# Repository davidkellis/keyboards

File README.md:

# TKL keyboard designs

Low-profile tenkeyless keyboard designs, from the original KiCad project to
later nRF52840 boards, case designs, and switch-plate lighting experiments.
The repository contains PCB and schematic sources, mechanical models,
manufacturing exports, firmware configuration notes, and interactive 3D viewers.

*V12 assembly visualization. Fit, lighting, and alternate switch-family support
still require physical prototype testing.*

## Start here

The latest revision is **[TKL v12](tkl/tkl12/README.md)**: an 86-key PCB with
soldered mounting patterns for Kailh Choc V1, Kailh Choc V2, and selected Gateron
Low Profile 3.0 switches. Its case and plate requirements depend on the chosen
switch family; see the [compatibility notes](tkl/tkl12/SWITCHES.md).

- **Explore the design:** clone or download the repository, then open
  `tkl/tkl12/render-switches/index.html` locally in Chrome or Brave. The
  [switch and keycap studio](tkl/tkl12/render-switches/README.md) works offline.
- **Open the CAD:** use [keyboard.kicad_pro](tkl/tkl12/kicad/keyboard.kicad_pro)
  in KiCad 10 to inspect the latest PCB and schematic.
- **Review fit models:** start with the
  [PCB models and switch-fit coupon](tkl/tkl12/case/README.md).
- **Review fabrication outputs:** read the
  [ordering notes](tkl/tkl12/manufacturing/ORDERING.md) and
  [fabrication instructions](tkl/tkl12/manufacturing/FABRICATION.md).
- **Check or regenerate exports:** follow the
  [revision's source and checking instructions](tkl/tkl12/scripts/README.md).

Recent revisions are prototypes with software validation records. Hardware
bring-up, switch and stabilizer travel, battery integration, and optical
performance still need physical testing. Read the chosen revision's notes and
[bring-up procedure](tkl/tkl12/BRINGUP.md) before ordering or assembling a board.

## Design revisions

Each major version has one commit. The original project is preserved as v0;
decimal variants stay with their major version. Earlier designs remain in
their own directories so their sources and design choices can be compared.

| Version | Design |
| --- | --- |
| [v0](tkl/tkl0/README.md) | Original KiCad project |
| [v1](tkl/tkl1/README.md) | Initial keyboard layout and KiCad design |
| [v2](tkl/tkl2/) | Early PCB and schematic revision |
| [v3](tkl/tkl3/) | Early PCB and schematic revision |
| [v4](tkl/tkl4/) | PCB and case design |
| [v5](tkl/tkl5/) | PCB and case refinement |
| [v6](tkl/tkl6/) | Controller-module board and case |
| [v7](tkl/tkl7/README.md) | Integrated nRF52840 design and v7.x alternatives |
| [v8](tkl/tkl8/README.md) | Top-mounted LED design |
| [v9](tkl/tkl9/README.md) | Direct rear USB module and v9.x case revisions |
| [v10](tkl/tkl10/README.md) | Esc/F1 controller position, case variants, and lighting studies |
| [v11](tkl/tkl11/README.md) | Reverse LEDs and acrylic switch plate |
| [v12](tkl/tkl12/README.md) | Multiple soldered low-profile switch families |

v7 alternatives: [v7.3](tkl/tkl7.3/README.md), [v7.4](tkl/tkl7.4/README.md),
and [v7.5](tkl/tkl7.5/README.md).

v9 case revisions: [v9.1](tkl/tkl9.1/README.md), [v9.2](tkl/tkl9.2/README.md),
and [v9.3](tkl/tkl9.3/README.md).

Shared [mechanical tools](tkl/mechanical/README.md), [research](tkl/research/),
and [handoff packaging](tkl/package_handoff.py) support the later designs.

## Finding the files

Recent revision directories use the following structure:

| Path | Contents |
| --- | --- |
| `kicad/` | PCB, schematic, project settings, and local component libraries |
| `case/` | Mechanical models, print-fit gauges, and fit documentation |
| `manufacturing/` | Gerbers and drills, BOM and placement files, assembly drawings, and ordering notes |
| `firmware/` | Controller, matrix, and lighting configuration references |
| `scripts/` | Design generation, export, and validation tools |
| `validation/` | Saved electrical, mechanical, and export check results |
| `reference/` | Manufacturer drawings, design studies, and preserved source records |
| `render-*/` | Browser viewers, assembly previews, and rendering sources |

The original v0 and v1 KiCad projects retain their `tkl.kicad_pro` filenames
directly inside `tkl/tkl0/` and `tkl/tkl1/`.

Use the PCB, manufacturing files, and mechanical parts from the same revision
unless its documentation explicitly identifies a compatible earlier part.
Print-fit gauges intentionally enlarge some holes; use the Gerber and drill
exports for PCB fabrication.

## Working with the sources

Recent electrical designs use KiCad 10. Python generators may need KiCad's
`pcbnew` module and additional geometry packages; mechanical tools use CadQuery,
and viewer generators have their own Python or Node dependencies. Follow the
instructions and dependency files beside the tool you want to run.

The final routed PCB is the source for normal checks and manufacturing exports.
Some revision-building scripts reset from an earlier baseline or change routing;
read their instructions before running them.

## Third-party credits

Rendering studies include third-party software and meshes. See the
[v12 viewer attributions](tkl/tkl12/render-switches/ATTRIBUTIONS.md) and the
attribution and license files included with each rendering study.

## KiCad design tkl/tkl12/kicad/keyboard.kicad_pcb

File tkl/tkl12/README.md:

# TKL V12 — three soldered low-profile switch families

V12 is a separate revision derived from the final routed V11 board. **V11 and
earlier revisions are preserved.** Open [the KiCad project](kicad/keyboard.kicad_pro)
or [the PCB](kicad/keyboard.kicad_pcb).

Explore the assembled keyboard in the new [V12 switch and keycap studio](render-switches/index.html):
switch families, matching keycap styles, both case editions, free 360° viewing,
exploded layers and lighting previews. Appearance and alternate-family mechanical
fit assumptions are explained in the [viewer notes](render-switches/README.md).

The board retains every original Kailh Choc V2 drill, copper land and switch
position. Each of the 86 keys gains two shared nonplated locating slots and two
Gateron electrical contacts. Choose one switch family for the build:

| Family | PCB mounting | Other parts needed |
| --- | --- | --- |
| Kailh Choc V2, including our Deep Sea Mini Whale | Original holes and contacts, unchanged | Existing Kailh plate height and MX-stem keycaps |
| Kailh Choc V1 | Original electrical contacts plus shared side slots | Choc two-slot keycaps; verify stabilizers and cap/case travel |
| Selected Gateron Low Profile 3.0 | Alternate contacts plus shared side slots | Plate top 2.5 mm above PCB instead of Kailh's 2.2 mm; verify keycap skirts, travel and optics |

These are **soldered footprints**, without hot-swap sockets. The exact Gateron
references and mounting drawing are in [SWITCHES.md](SWITCHES.md). This does not
claim compatibility with older Gateron generations, Cherry Low Profile or every
retail switch sold under a similar name.

The three-family pattern uses the same LED-facing direction. The earlier
feasibility study mixed top and bottom drawing views for Gateron; V12 corrects
that chirality and checks it against the official PCB drawing and KiCad's
standard MX footprint. One output capacitor, **C2**, moves from (117.8, 31) to
(124, 34.5) mm to clear the added contacts. All other component positions,
the boost switching loop, LED positions, matrix, controller pinout, board outline
and twelve M2 mounting holes remain unchanged.

## Assembly and cost

The target stays **two layers, 1.6 mm FR-4, lead-free HASL and lead-free Economic
bottom-side assembly**. The factory BOM is unchanged: ten purchasing groups and
106 placements, all on the bottom. Switches and the controller clone are fitted
by the user. The new holes do not add SMT placements or feeder types; extra
drilling/routing can still affect the fabrication quote. The current live quote is linked below; it retains the previous $29.05 fabrication price for five.

The ten reverse LEDs, TPS61169 driver, ZMK PWM interface and optional four-LED
wire bypass retain V11's circuit. See [bring-up instructions](BRINGUP.md).
Changing switch family does not require a different electrical matrix or pinmap.

## Files and checks

- [Front copper preview](front.svg) and [back copper preview](back.svg).
- [Switch mounting diagram](reference/switch-pattern.svg).
- [Manufacturing package](manufacturing/tkl-v12-prototype-handoff.zip), including
  Gerbers/drills, schematic PDF, assembly drawings, BOM and CPL.
- [Ordering settings](manufacturing/ORDERING.md) and [fabrication notes](manufacturing/FABRICATION.md).
- [Exact PCB STL](case/pcb-bare.stl) and [enlarged-hole print gauge](case/pcb-fit-check.stl).
- [Small three-position print-fit coupon](case/switch-fit-coupon.stl).
- [Electrical checks](validation/summary.json), [preservation and pattern audit](validation/revision-audit.json)
  and [export checks](validation/handoff-check.json).
- [Repeatable checking/export commands](scripts/README.md).

The existing V11/V10 case and plate remain the reference for our Kailh build;
V12 does not silently change their switch seating height. There is no completed
Gateron-height case/plate in this PCB revision. The print coupon checks pin and
peg alignment, not metal PCB tolerances, switch clip retention or optical performance.
Test real switches, plate, stabilizers and keycap travel before buying a complete
alternate-family build. Hardware, charging, RF and lighting still need prototype
bench tests; software checks do not establish physical performance.

Final software checks (KiCad 10, 2026-10-16): **0 ERC errors/warnings,
0 DRC errors/warnings, 0 unrouted connections and 0 schematic parity issues**.
All 86 keys and all 344 new holes are checked. The original V11's 470 saved
files are unchanged. Exported drill coordinates, archive hashes and 106 bottom
placements also pass; all three STL models are watertight.

The [live JLCPCB quote saved on 2026-10-16](manufacturing/quote-v12-2026-10-16/README.md)
is **$180.26 delivered for five assembled boards** using lead-free HASL,
lead-free Economic bottom-side assembly and UPS DDP, before any unpriced
reverse-LED handling/fixture charge after review. Nothing has been ordered or
paid. The displayed PCB fabrication price remains $29.05 for five.

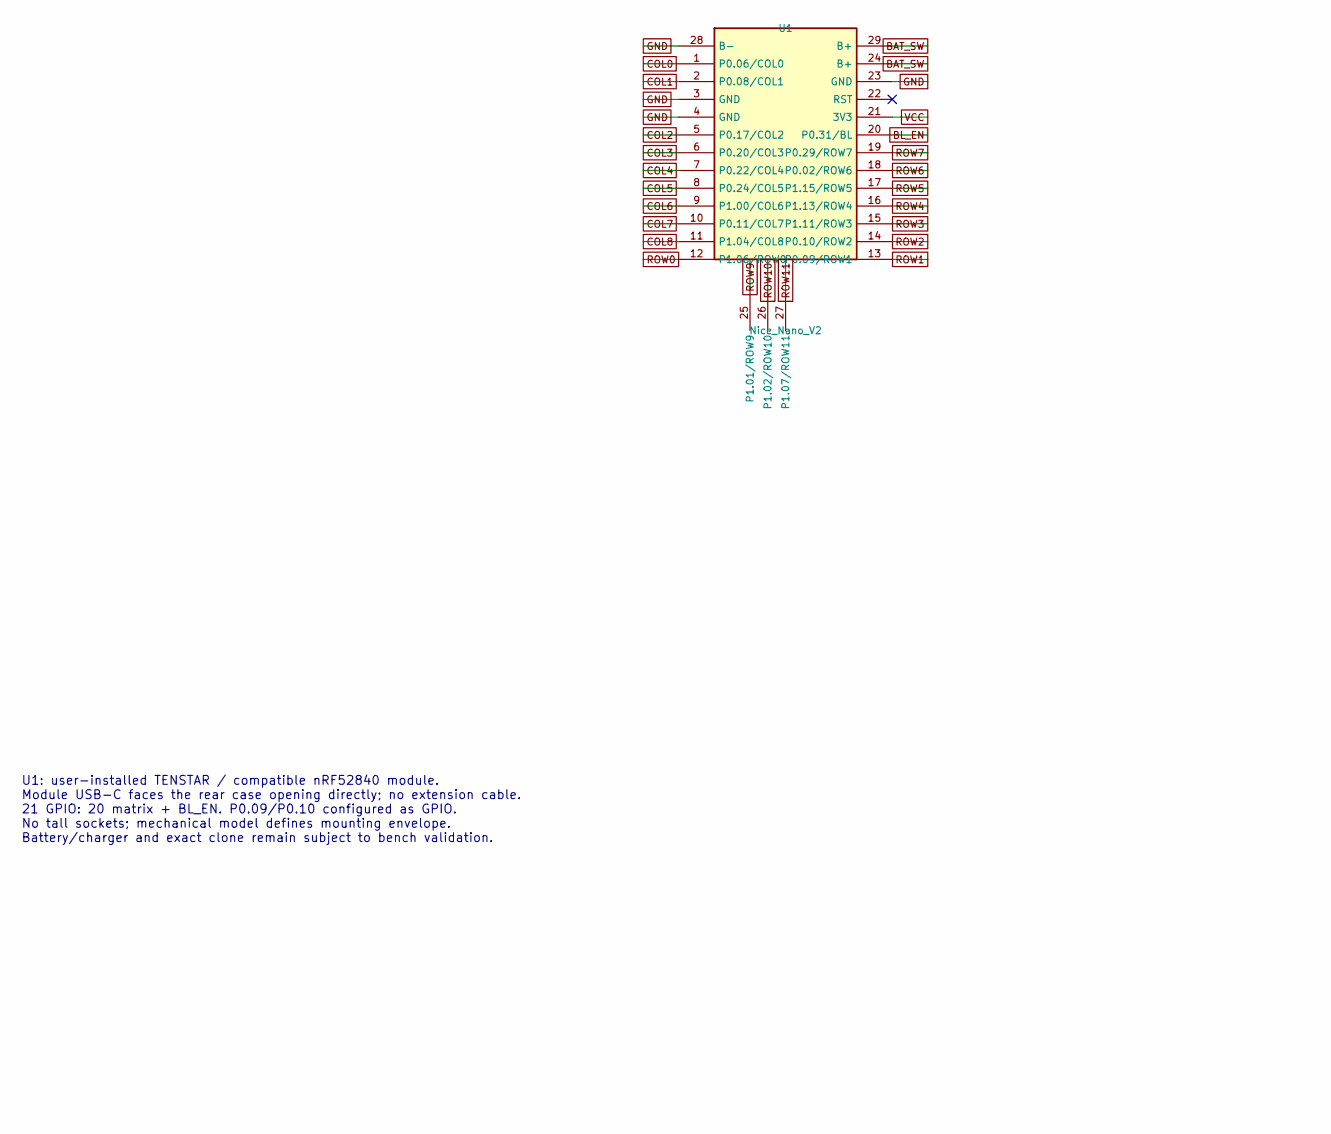
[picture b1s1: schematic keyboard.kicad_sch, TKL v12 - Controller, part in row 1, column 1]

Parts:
U1: Nice_Nano_V2; U1_Nice_Nano_V2

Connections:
BAT_SW: U1.24 (B+), U1.29 (B+); also elsewhere on the board
BL_EN: U1.20 (21); also elsewhere on the board
COL0: U1.1; also elsewhere on the board
COL1: U1.2 (0); also elsewhere on the board
COL2: U1.5 (2); also elsewhere on the board
COL3: U1.6 (3); also elsewhere on the board
COL4: U1.7 (4); also elsewhere on the board
COL5: U1.8 (5); also elsewhere on the board
COL6: U1.9 (6); also elsewhere on the board
COL7: U1.10 (7); also elsewhere on the board
COL8: U1.11 (8); also elsewhere on the board
GND: U1.3 (GND), U1.4 (GND), U1.23 (GND), U1.28 (B-); also elsewhere on the board
ROW0: U1.12 (9); also elsewhere on the board
ROW1: U1.13 (10); also elsewhere on the board
ROW2: U1.14 (16); also elsewhere on the board
ROW3: U1.15 (14); also elsewhere on the board
ROW4: U1.16 (15); also elsewhere on the board
ROW5: U1.17 (18); also elsewhere on the board
ROW6: U1.18 (19); also elsewhere on the board
ROW7: U1.19 (20); also elsewhere on the board
ROW9: U1.25 (1); also elsewhere on the board
ROW10: U1.26 (2); also elsewhere on the board
ROW11: U1.27 (7); also elsewhere on the board
VCC: U1.21 (3.3v)

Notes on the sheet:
U1: user-installed TENSTAR / compatible nRF52840 module. Module USB-C faces the rear case opening directly; no extension cable. 21 GPIO: 20 matrix + BL_EN. P0.09/P0.10 configured as GPIO. No tall sockets; mechanical model defines mounting envelope. Battery/charger and exact clone remain subject to 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

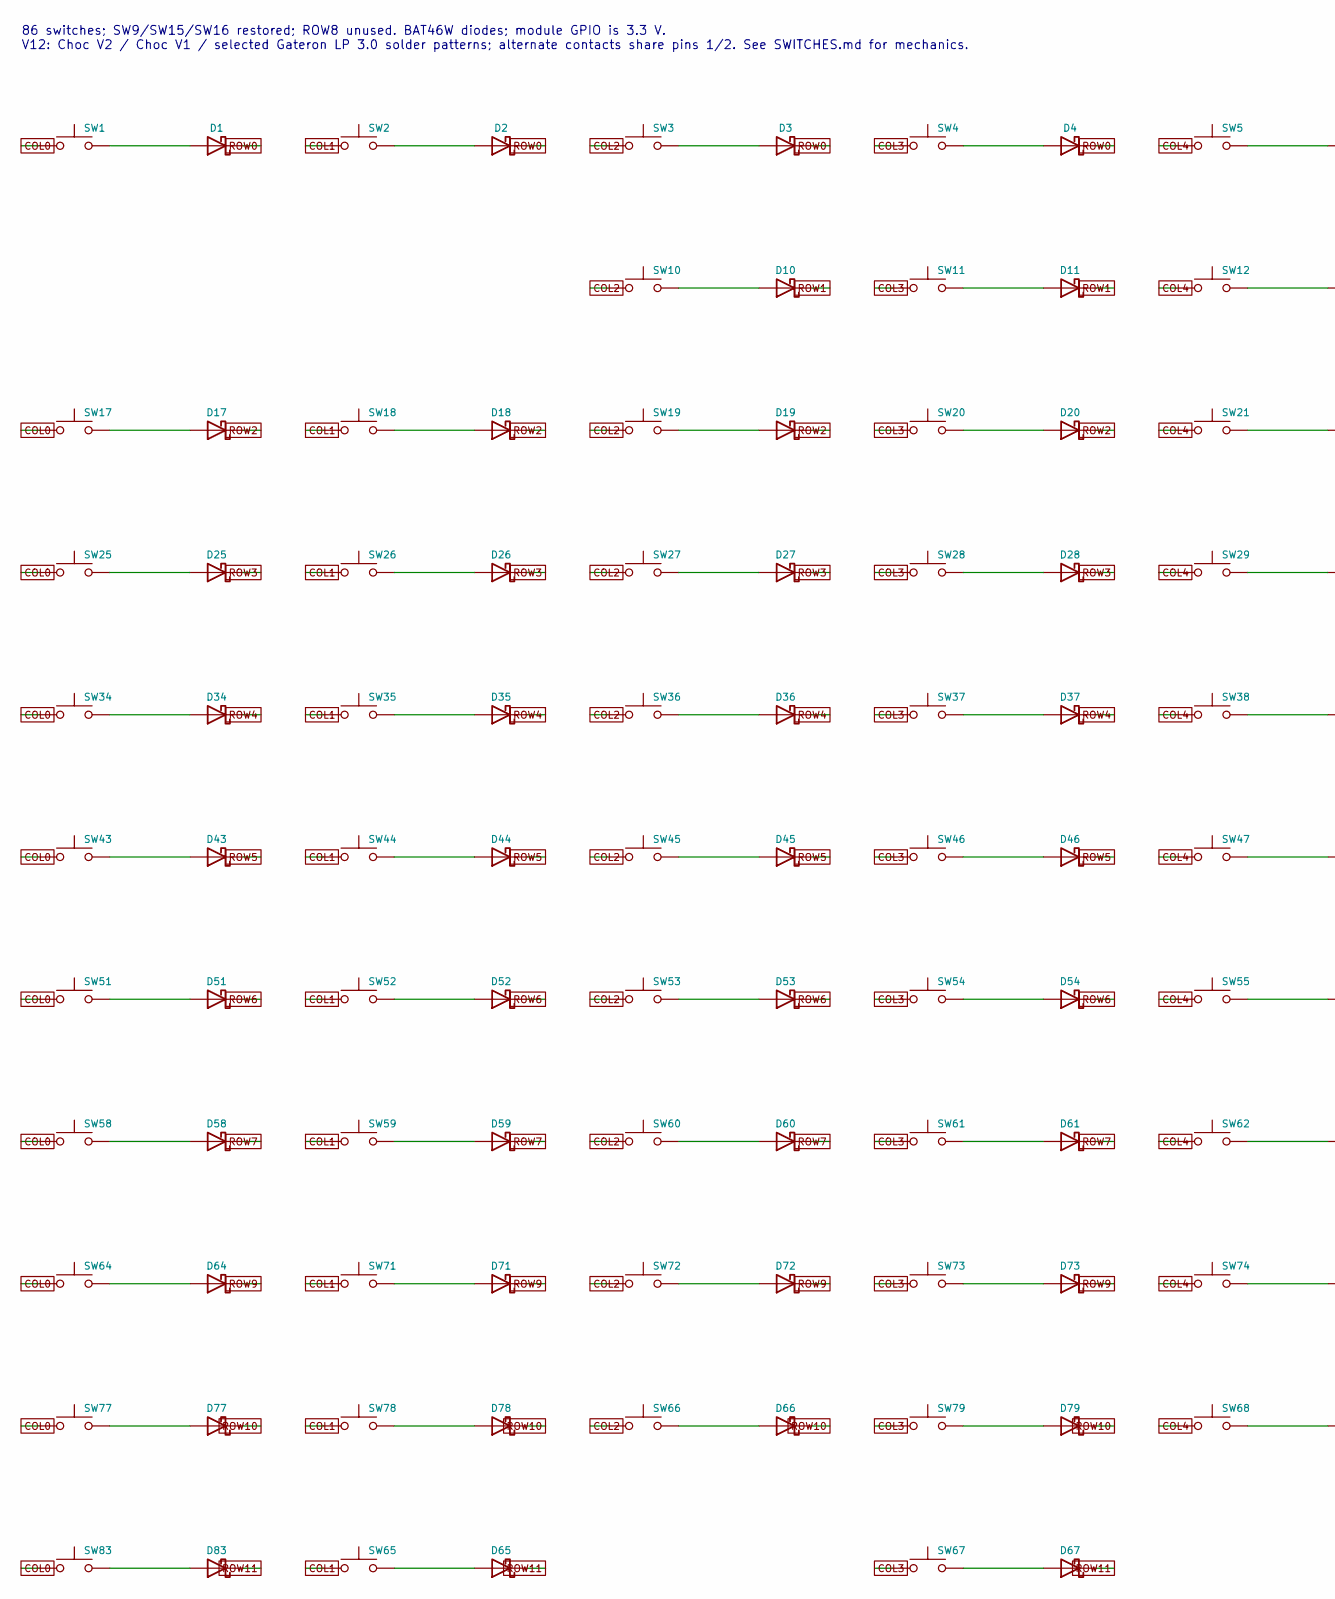
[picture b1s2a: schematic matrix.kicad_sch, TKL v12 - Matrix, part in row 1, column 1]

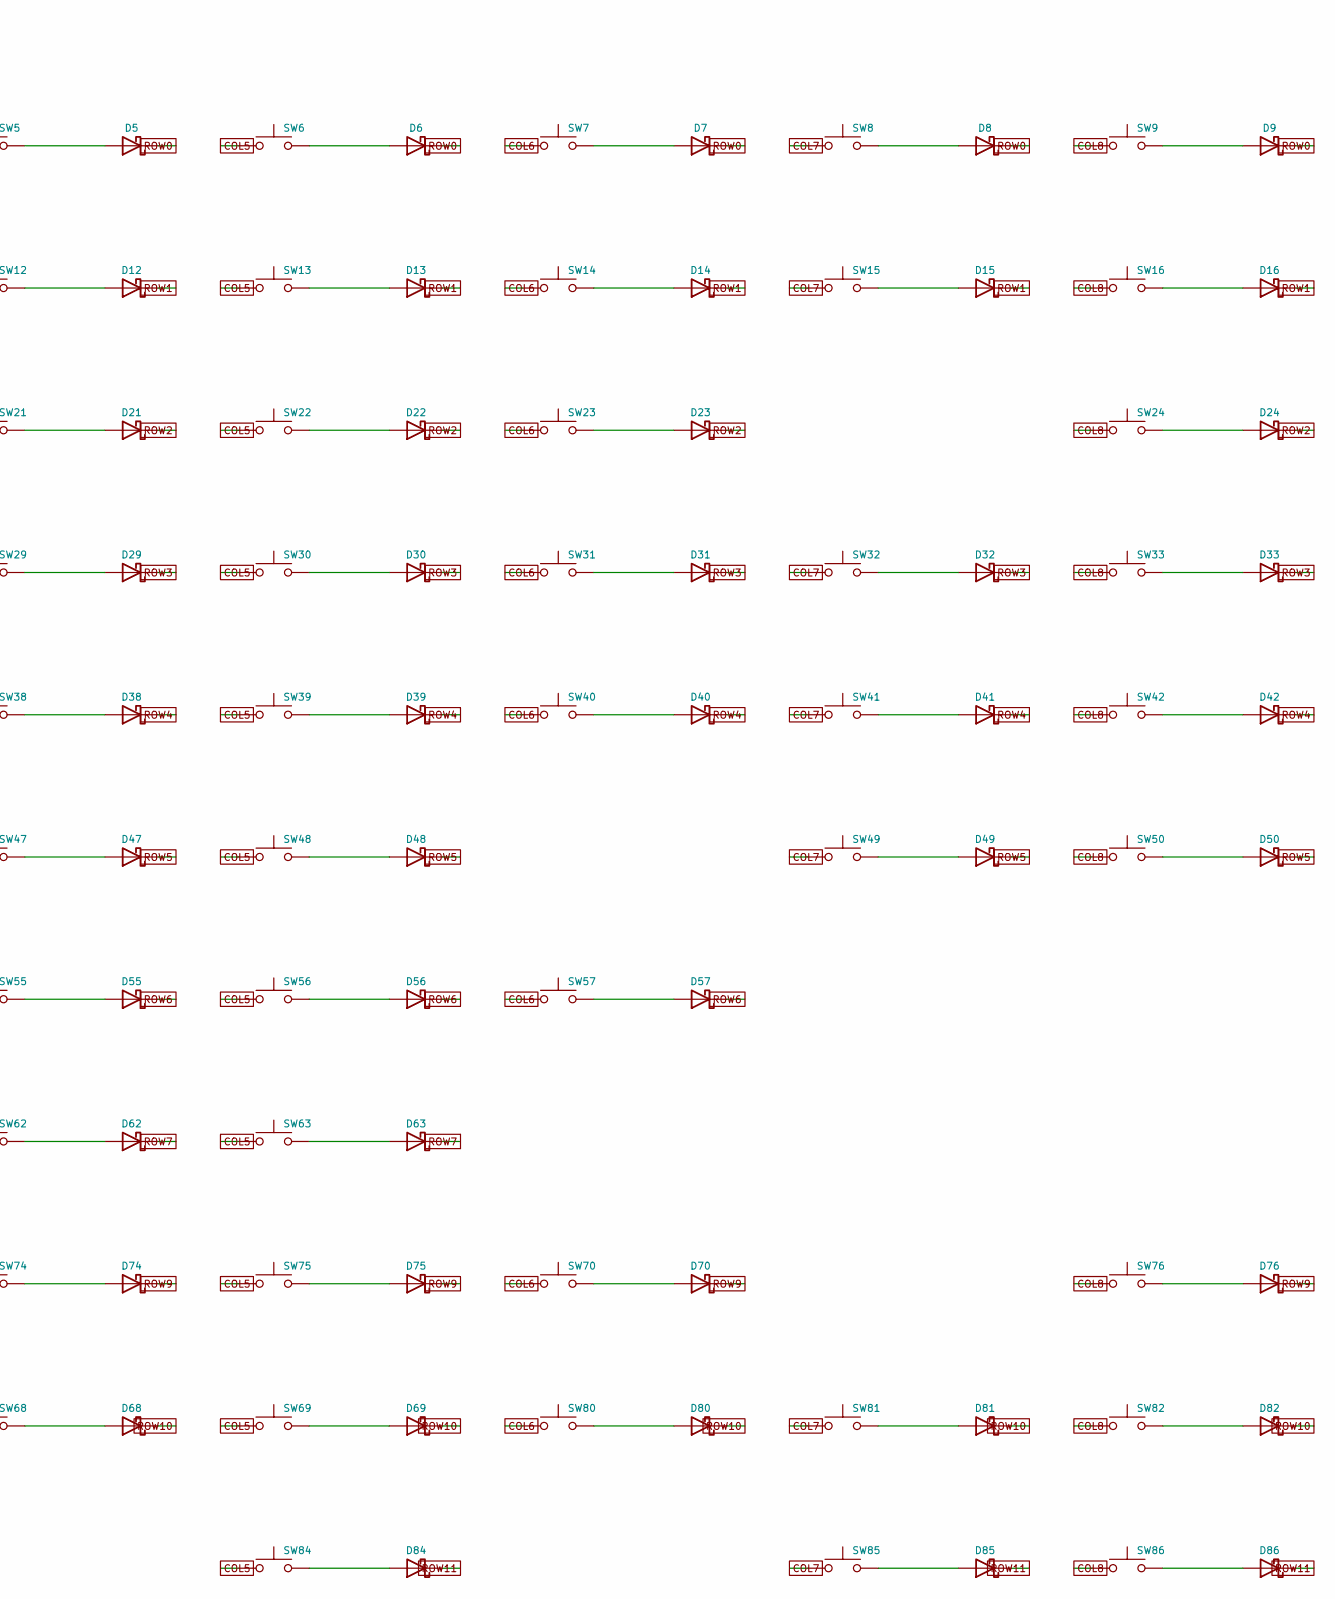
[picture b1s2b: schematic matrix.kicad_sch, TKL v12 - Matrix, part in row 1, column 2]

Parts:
D1, D2, D3, D4, D5, D6, D7, D8, D9, D10, D11, D12, D13, D14, D15, D16, D17, D18, D19, D20, D21, D22, D23, D24, D25, D26, D27, D28, D29, D30, D31, D32, D33, D34, D35, D36, D37, D38, D39, D40, D41, D42, D43, D44, D45, D46, D47, D48, D49, D50, D51, D52, D53, D54, D55, D56, D57, D58, D59, D60, D61, D62, D63, D64, D65, D66, D67, D68, D69, D70, D71, D72, D73, D74, D75, D76, D77, D78, D79, D80, D81, D82, D83, D84, D85, D86: BAT46W; D_SOD-123; MPN BAT46W; LCSC C54110
SW1, SW2, SW3, SW4, SW5, SW6, SW7, SW8, SW9, SW10, SW11, SW12, SW13, SW14, SW15, SW16, SW17, SW18, SW19, SW20, SW21, SW22, SW23, SW24, SW25, SW26, SW27, SW28, SW29, SW30, SW32, SW33, SW35, SW36, SW37, SW38, SW39, SW40, SW43, SW44, SW45, SW46, SW47, SW48, SW52, SW53, SW54, SW55, SW56, SW58, SW59, SW60, SW61, SW62, SW63, SW65, SW66, SW67, SW68, SW69, SW71, SW72, SW73, SW74, SW75, SW76, SW82, SW85, SW86: SW_Push; SW_LP_ThreeFamily_1.00u
SW31: SW_Push; SW_LP_ThreeFamily_2.00u
SW34, SW41, SW78, SW80, SW81, SW83, SW84: SW_Push; SW_LP_ThreeFamily_1.50u
SW42: SW_Push; SW42_SW_LP_ThreeFamily_1.00u
SW49: SW_Push; SW49_SW_LP_ThreeFamily_1.00u
SW50: SW_Push; SW50_SW_LP_ThreeFamily_1.00u
SW51: SW_Push; SW_LP_ThreeFamily_1.75u
SW57, SW64: SW_Push; SW_LP_ThreeFamily_2.25u
SW70: SW_Push; SW_LP_ThreeFamily_2.75u
SW77: SW_Push; SW_LP_ThreeFamily_1.25u
SW79: SW_Push; SW_LP_ThreeFamily_6.25u

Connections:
COL0: SW1.1, SW17.1, SW25.1, SW34.1, SW43.1, SW51.1, SW58.1, SW64.1, SW77.1, SW83.1; also elsewhere on the board
COL1: SW2.1, SW18.1, SW26.1, SW35.1, SW44.1, SW52.1, SW59.1, SW65.1, SW71.1, SW78.1; also elsewhere on the board
COL2: SW3.1, SW10.1, SW19.1, SW27.1, SW36.1, SW45.1, SW53.1, SW60.1, SW66.1, SW72.1; also elsewhere on the board
COL3: SW4.1, SW11.1, SW20.1, SW28.1, SW37.1, SW46.1, SW54.1, SW61.1, SW67.1, SW73.1, SW79.1; also elsewhere on the board
COL4: SW5.1, SW12.1, SW21.1, SW29.1, SW38.1, SW47.1, SW55.1, SW62.1, SW68.1, SW74.1; also elsewhere on the board
COL5: SW6.1, SW13.1, SW22.1, SW30.1, SW39.1, SW48.1, SW56.1, SW63.1, SW69.1, SW75.1, SW84.1; also elsewhere on the board
COL6: SW7.1, SW14.1, SW23.1, SW31.1, SW40.1, SW57.1, SW70.1, SW80.1; also elsewhere on the board
COL7: SW8.1, SW15.1, SW32.1, SW41.1, SW49.1, SW81.1, SW85.1; also elsewhere on the board
COL8: SW9.1, SW16.1, SW24.1, SW33.1, SW42.1, SW50.1, SW76.1, SW82.1, SW86.1; also elsewhere on the board
unnamed: D1.2 (A), SW1.2
unnamed: D2.2 (A), SW2.2
unnamed: D3.2 (A), SW3.2
unnamed: D4.2 (A), SW4.2
unnamed: D5.2 (A), SW5.2
unnamed: D6.2 (A), SW6.2
unnamed: D7.2 (A), SW7.2
unnamed: D8.2 (A), SW8.2
unnamed: D9.2 (A), SW9.2
unnamed: D10.2 (A), SW10.2
unnamed: D11.2 (A), SW11.2
unnamed: D12.2 (A), SW12.2
unnamed: D13.2 (A), SW13.2
unnamed: D14.2 (A), SW14.2
unnamed: D15.2 (A), SW15.2
unnamed: D16.2 (A), SW16.2
unnamed: D17.2 (A), SW17.2
unnamed: D18.2 (A), SW18.2
unnamed: D19.2 (A), SW19.2
unnamed: D20.2 (A), SW20.2
unnamed: D21.2 (A), SW21.2
unnamed: D22.2 (A), SW22.2
unnamed: D23.2 (A), SW23.2
unnamed: D24.2 (A), SW24.2
unnamed: D25.2 (A), SW25.2
unnamed: D26.2 (A), SW26.2
unnamed: D27.2 (A), SW27.2
unnamed: D28.2 (A), SW28.2
unnamed: D29.2 (A), SW29.2
unnamed: D30.2 (A), SW30.2
unnamed: D31.2 (A), SW31.2
unnamed: D32.2 (A), SW32.2
unnamed: D33.2 (A), SW33.2
unnamed: D34.2 (A), SW34.2
unnamed: D35.2 (A), SW35.2
unnamed: D36.2 (A), SW36.2
unnamed: D37.2 (A), SW37.2
unnamed: D38.2 (A), SW38.2
unnamed: D39.2 (A), SW39.2
unnamed: D40.2 (A), SW40.2
unnamed: D41.2 (A), SW41.2
unnamed: D42.2 (A), SW42.2
unnamed: D43.2 (A), SW43.2
unnamed: D44.2 (A), SW44.2
unnamed: D45.2 (A), SW45.2
unnamed: D46.2 (A), SW46.2
unnamed: D47.2 (A), SW47.2
unnamed: D48.2 (A), SW48.2
unnamed: D49.2 (A), SW49.2
unnamed: D50.2 (A), SW50.2
unnamed: D51.2 (A), SW51.2
unnamed: D52.2 (A), SW52.2
unnamed: D53.2 (A), SW53.2
unnamed: D54.2 (A), SW54.2
unnamed: D55.2 (A), SW55.2
unnamed: D56.2 (A), SW56.2
unnamed: D57.2 (A), SW57.2
unnamed: D58.2 (A), SW58.2
unnamed: D59.2 (A), SW59.2
unnamed: D60.2 (A), SW60.2
unnamed: D61.2 (A), SW61.2
unnamed: D62.2 (A), SW62.2
unnamed: D63.2 (A), SW63.2
unnamed: D64.2 (A), SW64.2
unnamed: D65.2 (A), SW65.2
unnamed: D66.2 (A), SW66.2
unnamed: D67.2 (A), SW67.2
unnamed: D68.2 (A), SW68.2
unnamed: D69.2 (A), SW69.2
unnamed: D70.2 (A), SW70.2
unnamed: D71.2 (A), SW71.2
unnamed: D72.2 (A), SW72.2
unnamed: D73.2 (A), SW73.2
unnamed: D74.2 (A), SW74.2
unnamed: D75.2 (A), SW75.2
unnamed: D76.2 (A), SW76.2
unnamed: D77.2 (A), SW77.2
unnamed: D78.2 (A), SW78.2
unnamed: D79.2 (A), SW79.2
unnamed: D80.2 (A), SW80.2
unnamed: D81.2 (A), SW81.2
unnamed: D82.2 (A), SW82.2
unnamed: D83.2 (A), SW83.2
unnamed: D84.2 (A), SW84.2
unnamed: D85.2 (A), SW85.2
unnamed: D86.2 (A), SW86.2
ROW0: D1.1 (K), D2.1 (K), D3.1 (K), D4.1 (K), D5.1 (K), D6.1 (K), D7.1 (K), D8.1 (K), D9.1 (K); also elsewhere on the board
ROW1: D10.1 (K), D11.1 (K), D12.1 (K), D13.1 (K), D14.1 (K), D15.1 (K), D16.1 (K); also elsewhere on the board
ROW2: D17.1 (K), D18.1 (K), D19.1 (K), D20.1 (K), D21.1 (K), D22.1 (K), D23.1 (K), D24.1 (K); also elsewhere on the board
ROW3: D25.1 (K), D26.1 (K), D27.1 (K), D28.1 (K), D29.1 (K), D30.1 (K), D31.1 (K), D32.1 (K), D33.1 (K); also elsewhere on the board
ROW4: D34.1 (K), D35.1 (K), D36.1 (K), D37.1 (K), D38.1 (K), D39.1 (K), D40.1 (K), D41.1 (K), D42.1 (K); also elsewhere on the board
ROW5: D43.1 (K), D44.1 (K), D45.1 (K), D46.1 (K), D47.1 (K), D48.1 (K), D49.1 (K), D50.1 (K); also elsewhere on the board
ROW6: D51.1 (K), D52.1 (K), D53.1 (K), D54.1 (K), D55.1 (K), D56.1 (K), D57.1 (K); also elsewhere on the board
ROW7: D58.1 (K), D59.1 (K), D60.1 (K), D61.1 (K), D62.1 (K), D63.1 (K); also elsewhere on the board
ROW9: D64.1 (K), D70.1 (K), D71.1 (K), D72.1 (K), D73.1 (K), D74.1 (K), D75.1 (K), D76.1 (K); also elsewhere on the board
ROW10: D66.1 (K), D68.1 (K), D69.1 (K), D77.1 (K), D78.1 (K), D79.1 (K), D80.1 (K), D81.1 (K), D82.1 (K); also elsewhere on the board
ROW11: D65.1 (K), D67.1 (K), D83.1 (K), D84.1 (K), D85.1 (K), D86.1 (K); also elsewhere on the board

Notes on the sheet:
86 switches; SW9/SW15/SW16 restored; ROW8 unused. BAT46W diodes; module GPIO is 3.3 V. V12: Choc V2 / Choc V1 / selected Gateron LP 3.0 solder patterns; alternate contacts share pins 1/2. See SWITCHES.md for mechanics.

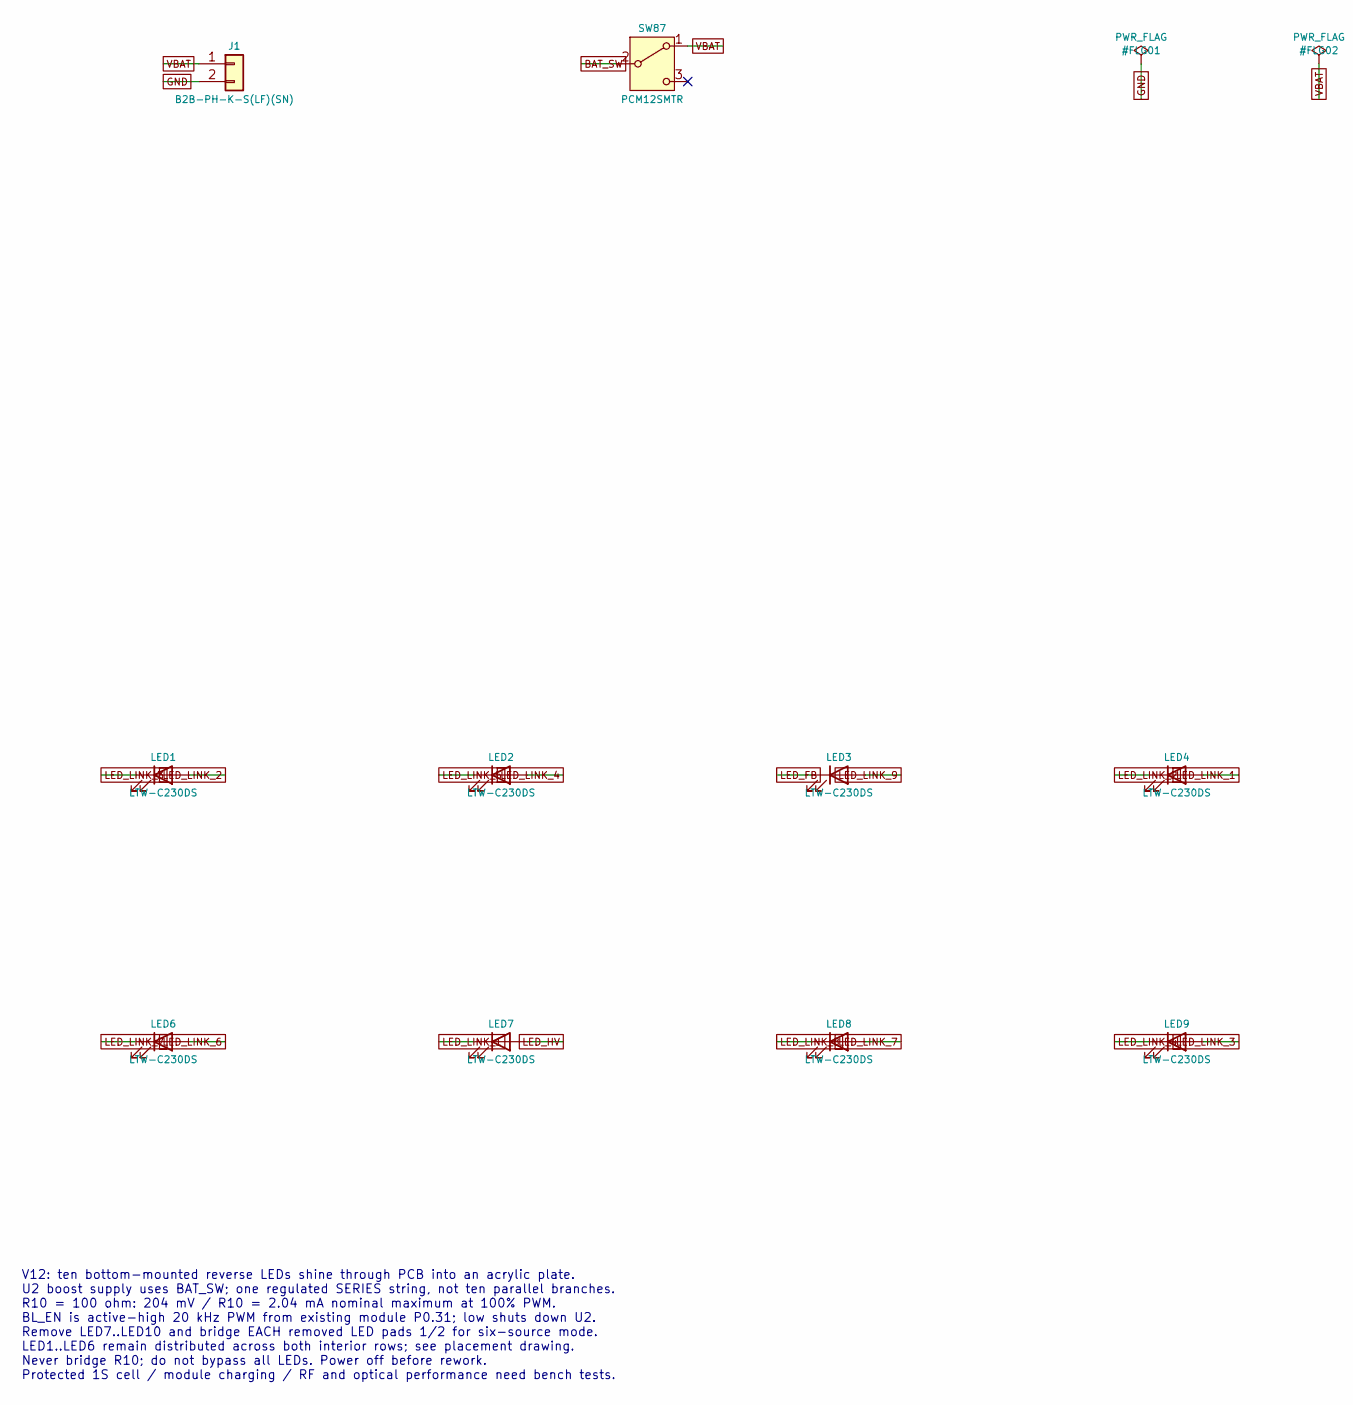
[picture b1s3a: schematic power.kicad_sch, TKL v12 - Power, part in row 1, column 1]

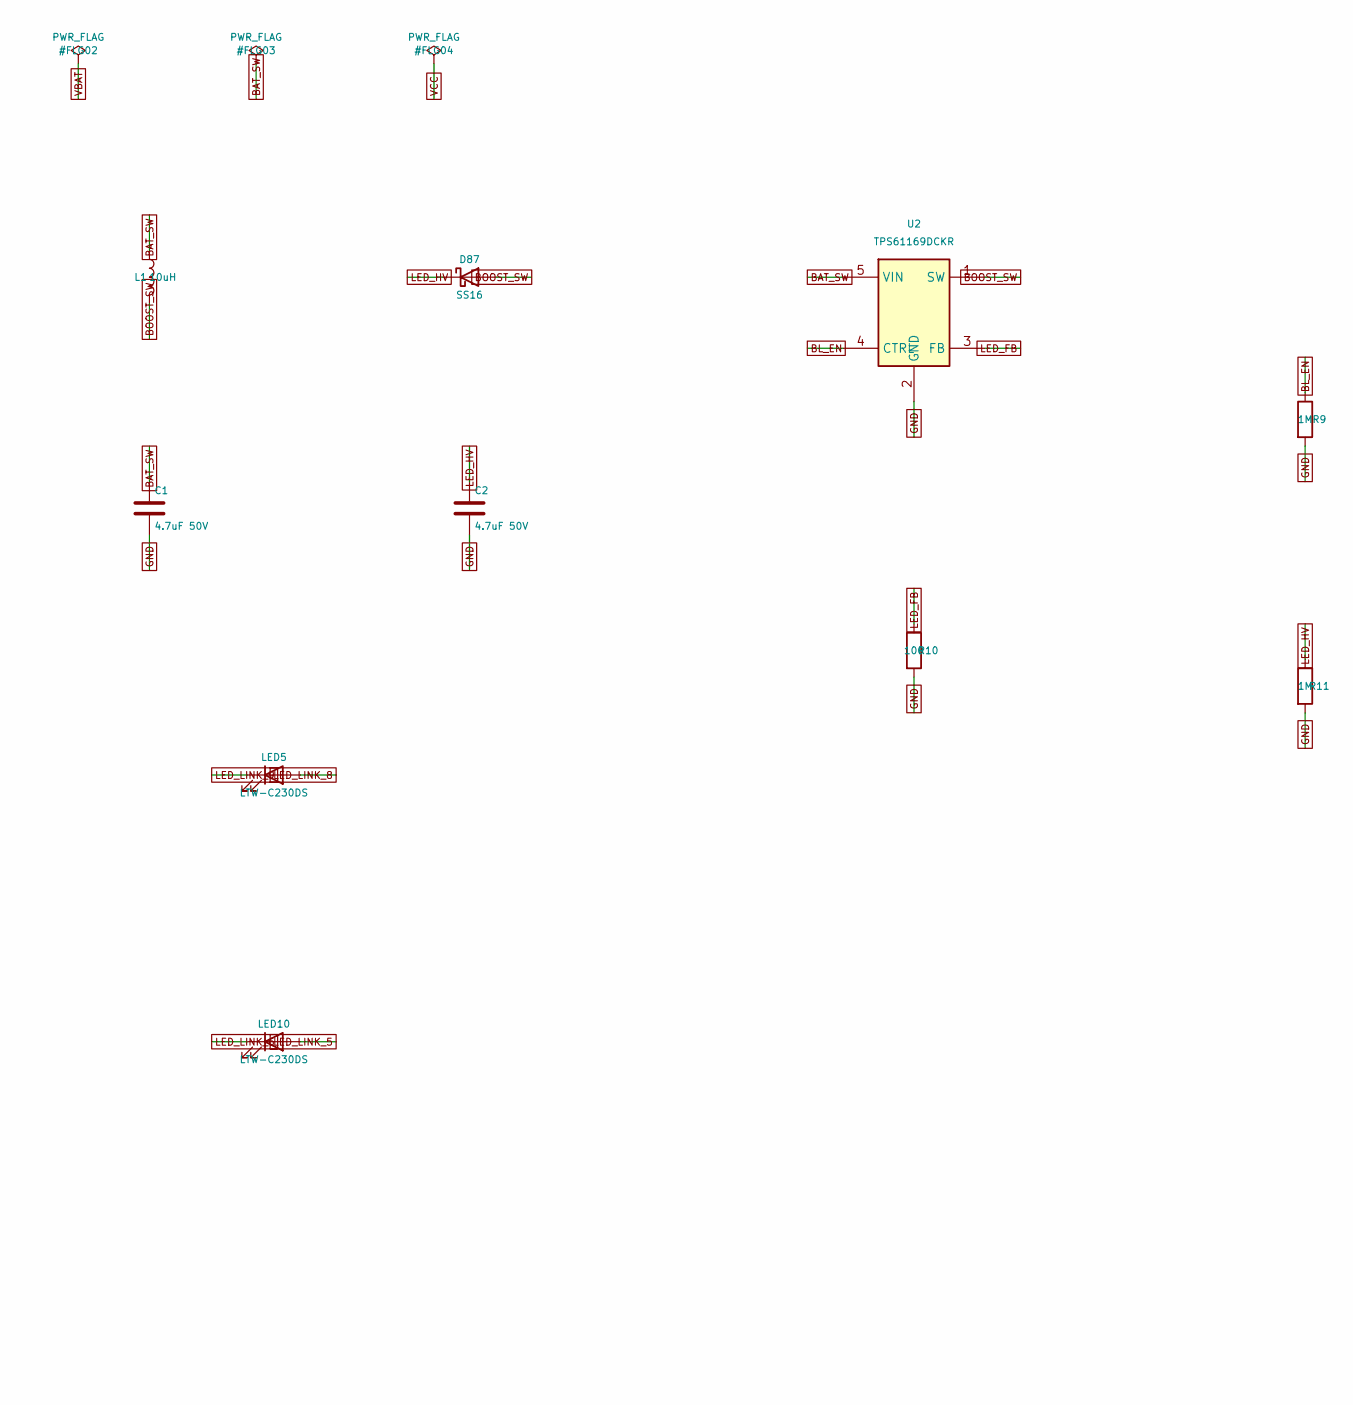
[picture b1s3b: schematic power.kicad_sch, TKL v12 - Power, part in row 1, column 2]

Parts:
C1, C2: 4.7uF 50V; C_1206_3216Metric; MPN CL31B475KBHNNNE; LCSC C51205
D87: SS16; D_SMA; MPN SS16; LCSC C3034074
J1: B2B-PH-K-S(LF)(SN); J1_JST_PH_B2B-PH-K_1x02_P2.00mm_Vertical; MPN B2B-PH-K-S(LF)(SN); LCSC C131337
L1: 10uH; L_Sunlord_SWPA4018S; MPN FNR4018S100MT; LCSC C167808
LED1, LED7, LED8, LED9, LED10: LTW-C230DS; LED1_LTW-C230DS_ReverseMount_Hole2.1x2.8; MPN LTW-C230DS; LCSC C575513
LED2: LTW-C230DS; LED2_LTW-C230DS_ReverseMount_Hole2.1x2.8; MPN LTW-C230DS; LCSC C575513
LED3: LTW-C230DS; LED3_LTW-C230DS_ReverseMount_Hole2.1x2.8; MPN LTW-C230DS; LCSC C575513
LED4: LTW-C230DS; LED4_LTW-C230DS_ReverseMount_Hole2.1x2.8; MPN LTW-C230DS; LCSC C575513
LED5: LTW-C230DS; LED5_LTW-C230DS_ReverseMount_Hole2.1x2.8; MPN LTW-C230DS; LCSC C575513
LED6: LTW-C230DS; LED6_LTW-C230DS_ReverseMount_Hole2.1x2.8; MPN LTW-C230DS; LCSC C575513
R9: 1M; R9_R_0603; MPN 0603WAF1004T5E; LCSC C22935
R10: 100; R_0603_1608Metric; MPN 0603WAF1000T5E; LCSC C22775
R11: 1M; R_0603_1608Metric; MPN 0603WAF1004T5E; LCSC C22935
SW87: PCM12SMTR; SW87_SW_SPDT_PCM12; MPN PCM12SMTR; LCSC C221841
U2: TPS61169DCKR; SOT-353_SC-70-5; MPN TPS61169DCKR; LCSC C71045

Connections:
BAT_SW: C1.1, L1.1, SW87.2 (B), U2.5 (VIN); also elsewhere on the board
BL_EN: R9.1, U2.4 (CTRL); also elsewhere on the board
BOOST_SW: D87.2 (A), L1.2, U2.1 (SW)
GND: C1.2, C2.2, J1.2, R9.2, R10.2, R11.2, U2.2 (GND); also elsewhere on the board
LED_FB: LED3.1 (K), R10.1, U2.3 (FB)
LED_HV: C2.1, D87.1 (K), LED7.2 (A), R11.1
LED_LINK_1: LED4.2 (A), LED7.1 (K)
LED_LINK_2: LED1.2 (A), LED4.1 (K)
LED_LINK_3: LED1.1 (K), LED9.2 (A)
LED_LINK_4: LED2.2 (A), LED9.1 (K)
LED_LINK_5: LED2.1 (K), LED10.2 (A)
LED_LINK_6: LED6.2 (A), LED10.1 (K)
LED_LINK_7: LED6.1 (K), LED8.2 (A)
LED_LINK_8: LED5.2 (A), LED8.1 (K)
LED_LINK_9: LED3.2 (A), LED5.1 (K)
VBAT: J1.1, SW87.1 (A)

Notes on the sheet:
V12: ten bottom-mounted reverse LEDs shine through PCB into an acrylic plate. U2 boost supply uses BAT_SW; one regulated SERIES string, not ten parallel branches. R10 = 100 ohm: 204 mV / R10 = 2.04 mA nominal maximum at 100% PWM. BL_EN is active-high 20 kHz PWM from existing module P0.31; low shuts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

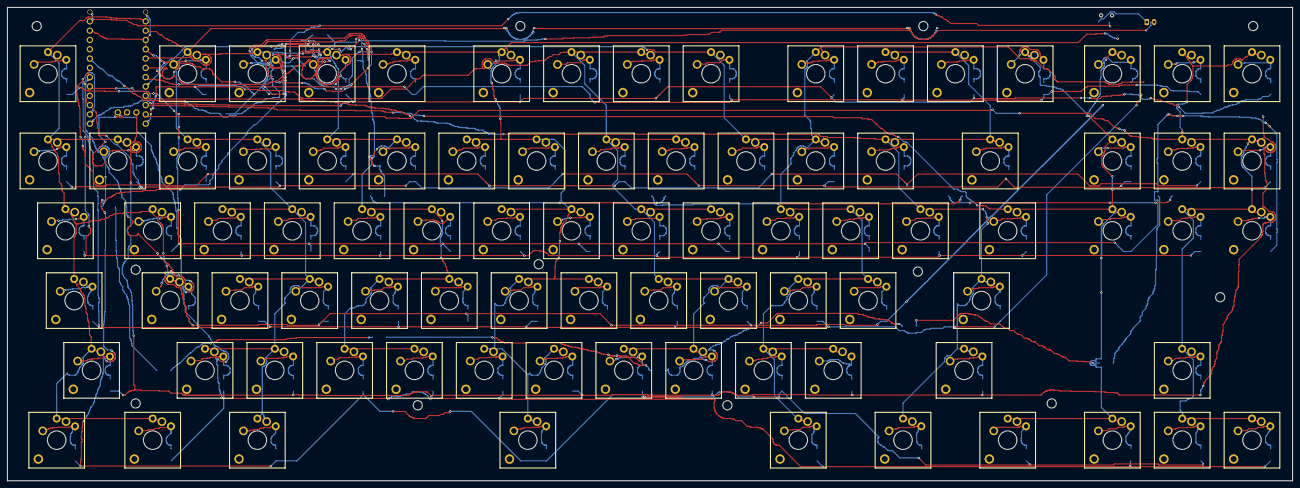
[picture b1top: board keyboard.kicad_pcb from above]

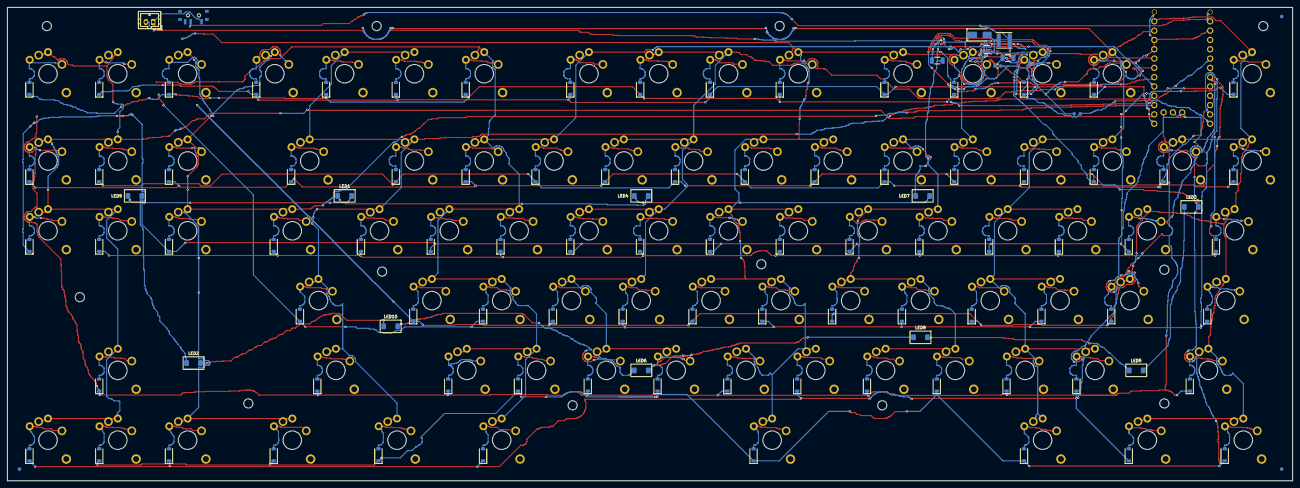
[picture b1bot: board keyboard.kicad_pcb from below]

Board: 2 copper layers, 350.8 x 129.2 mm, 208 parts (110 on the bottom side), 122 nets.

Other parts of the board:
FID1, FID2, FID3: Fiducial; Fiducial_1mm_Mask2mm
H1, H2, H3, H4, H5, H6, H7, H8, H9, H10, H11, H12: Mount_M2_2.5mm
